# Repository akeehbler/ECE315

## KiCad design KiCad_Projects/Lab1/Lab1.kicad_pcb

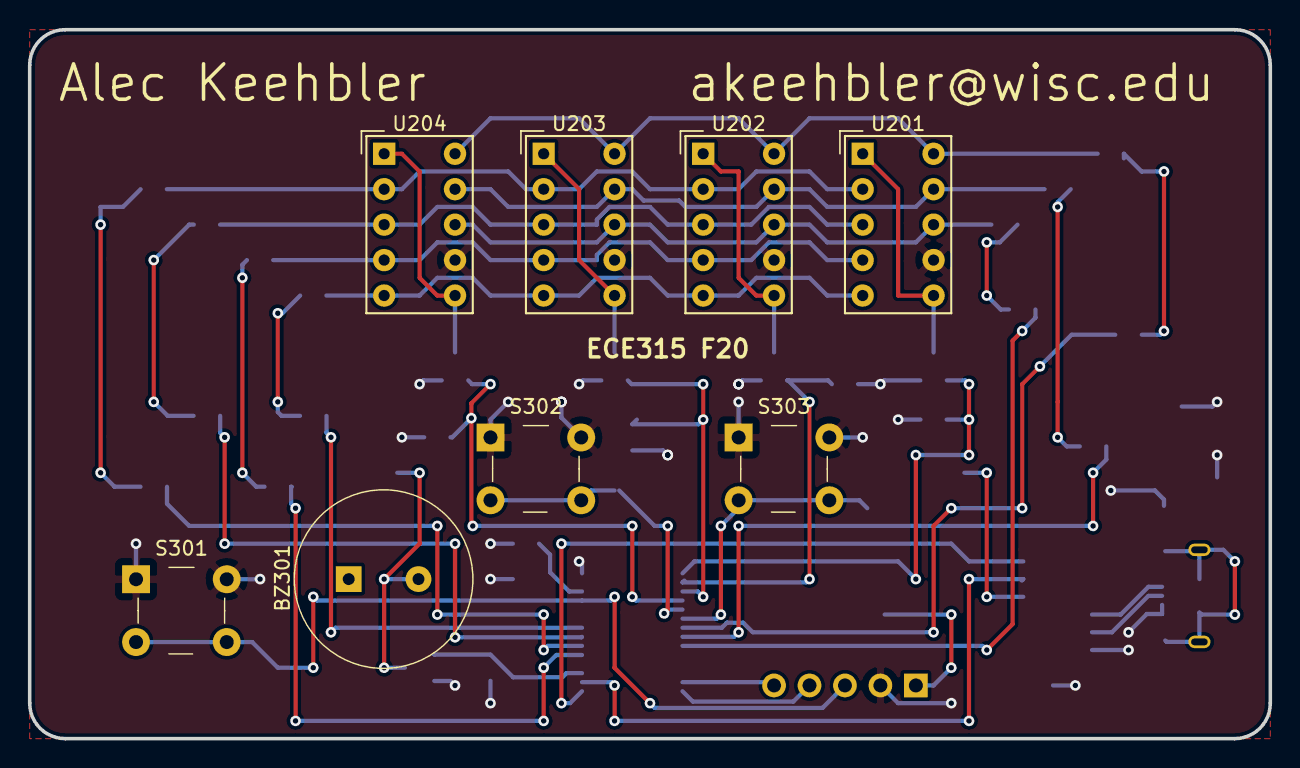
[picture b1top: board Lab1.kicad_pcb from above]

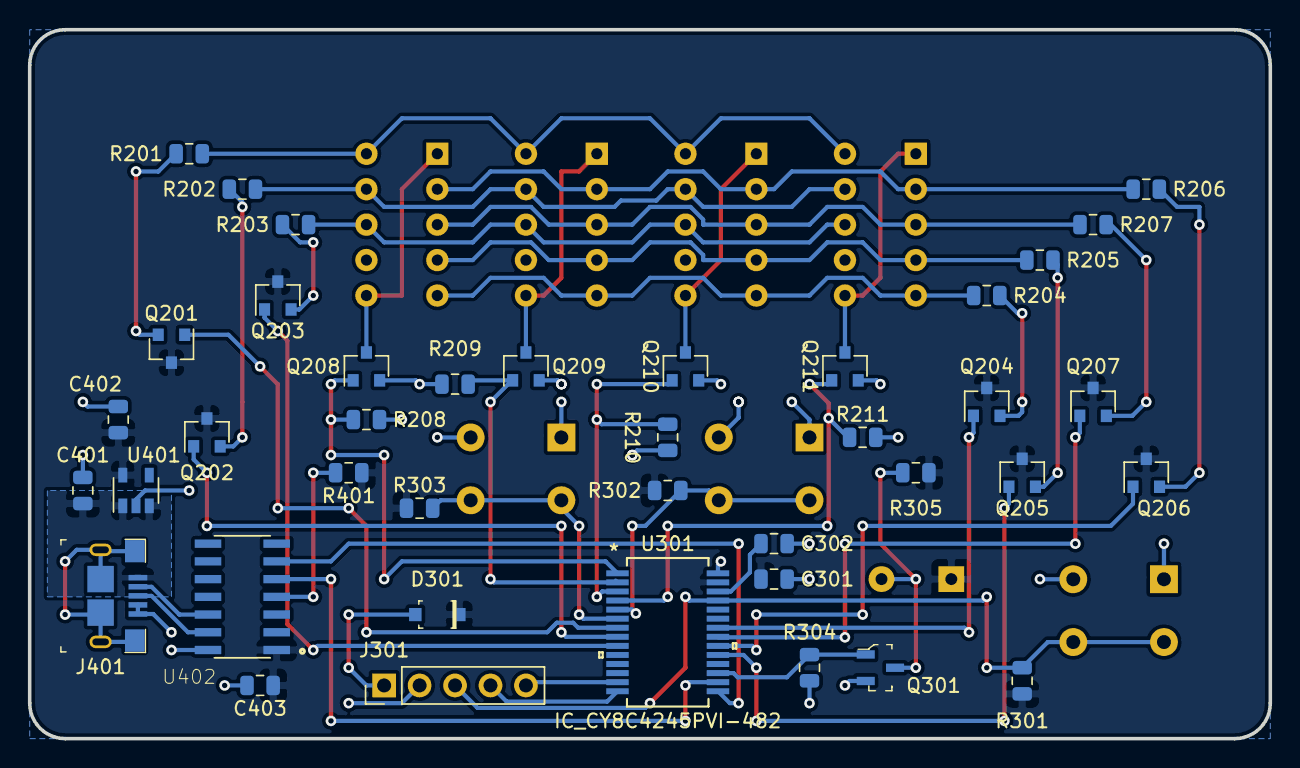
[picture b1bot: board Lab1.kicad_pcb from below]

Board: 2 copper layers, 88.9 x 50.8 mm, 48 parts (40 on the bottom side), 46 nets.

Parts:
BZ301: PS1240P02BT; Piezo_Transducer_THT_PS1240P02BT
C301, C302, C401, C402, C403: 10uF; C_0805_2012Metric
D301: 1N5819HW-7-F; SOD-123
J301: Conn_01x05_Male; PinHeader_1x05_P2.54mm_Vertical
J401: 10118193-0001LF; USB_Micro_B_Female_10118193-0001LF
Q201, Q202, Q203, Q204, Q205, Q206, Q207: BSS84; SOT-23
Q208, Q209, Q210, Q211: BSN20; SOT-23
Q301: BC817-25-TP; SOT-23-3
R201, R202, R203, R204, R205, R206, R207, R305: 1K; R_0805_2012Metric
R208, R209, R210, R211, R301, R302, R303, R304, R401: 10K; R_0805_2012Metric
S301, S302, S303: B3F-1000; Switch_Tactile_THT_B3F-1xxx
U201, U202, U203, U204: HDSP-7403; HDSP-7401
U301: IC_CY8C4245PVI-482; CY8C4245PVI-482
U401: TLV71333PDBV; SOT-23-5
U402: MCP2221A-I_SL; SOIC127P600X175-14N

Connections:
+3V3: BZ301.1, C301.1, C402.1, C403.1, D301.K, Q201.3, Q202.3, Q203.3, Q204.3, Q205.3, Q206.3, Q207.3, R301.1, R302.1, R303.1, R305.1, R401.1, U301.27, U401.5, U402.1
+5V: C401.1, J401.1, U401.1, U401.3
/02_Display.sch/DIG0: Q208.3, U201.1, U201.6
/02_Display.sch/DIG0_EN: Q208.1, R208.1, U301.1
/02_Display.sch/DIG1: Q209.3, U202.1, U202.6
/02_Display.sch/DIG1_EN: Q209.1, R209.1, U301.2
/02_Display.sch/DIG2: Q210.3, U203.1, U203.6
/02_Display.sch/DIG2_EN: Q210.1, R210.1, U301.3
/02_Display.sch/DIG3: Q211.3, U204.1, U204.6
/02_Display.sch/DIG3_EN: Q211.1, R211.1, U301.4
/02_Display.sch/SEG_A: Q201.1, U301.7
/02_Display.sch/SEG_A_Q: Q201.2, R201.2
/02_Display.sch/SEG_A_R: R201.1, U201.10, U202.10, U203.10, U204.10
/02_Display.sch/SEG_B: Q202.1, U301.8
/02_Display.sch/SEG_B_Q: Q202.2, R202.2
/02_Display.sch/SEG_B_R: R202.1, U201.9, U202.9, U203.9, U204.9
/02_Display.sch/SEG_C: Q203.1, U301.9
/02_Display.sch/SEG_C_Q: Q203.2, R203.2
/02_Display.sch/SEG_C_R: R203.1, U201.8, U202.8, U203.8, U204.8
/02_Display.sch/SEG_D: Q204.1, U301.22
/02_Display.sch/SEG_D_Q: Q204.2, R204.2
/02_Display.sch/SEG_D_R: R204.1, U201.5, U202.5, U203.5, U204.5
/02_Display.sch/SEG_E: Q205.1, U301.19
/02_Display.sch/SEG_E_Q: Q205.2, R205.2
/02_Display.sch/SEG_E_R: R205.1, U201.4, U202.4, U203.4, U204.4
/02_Display.sch/SEG_F: Q206.1, U301.20
/02_Display.sch/SEG_F_Q: Q206.2, R206.2
/02_Display.sch/SEG_F_R: R206.1, U201.2, U202.2, U203.2, U204.2
/02_Display.sch/SEG_G: Q207.1, U301.21
/02_Display.sch/SEG_G_Q: Q207.2, R207.2
/02_Display.sch/SEG_G_R: R207.1, U201.3, U202.3, U203.3, U204.3
/03_MCU/BUZZER_N: BZ301.2, Q301.3, R305.2
/04_PWR/MCP_URX: U301.16, U402.5
/04_PWR/MCP_UTX: U301.15, U402.6
BTN_0: R302.2, S302.3, S302.4, U301.5
BTN_1: R303.2, S303.3, S303.4, U301.6
BUZZER: Q301.1, R304.1, U301.17
GND: C301.2, C302.2, C401.2, C402.2, C403.2, J301.2, J401.4, J401.5, Q208.2, Q209.2, Q210.2, Q211.2, Q301.2, R208.2, R209.2, R210.2, R211.2, R304.2, S301.1, S301.2, S302.1, S302.2, S303.1, S303.2, U201.7, U202.7, U203.7, U204.7, U301.28, U401.2, U402.14
MCU_SCLK: J301.4, U301.14
MCU_SWD: J301.5, U301.13
MCU_XRES_N: J301.3, R301.2, S301.3, S301.4, U301.25
unnamed: C302.1, U301.26
unnamed: D301.A, J301.1
unnamed: J401.2, U402.12
unnamed: J401.3, U402.13
unnamed: R401.2, U402.4

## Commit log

2020-12-03 Touch sensor mostly complete
2020-12-03 Added labels
2020-12-03 Fixed labels
2020-12-03 Adding Temp Sensor, also annotated

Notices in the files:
parts and their libraries:
Copyright 2016 Accelerated Designs. All rights reserved.
